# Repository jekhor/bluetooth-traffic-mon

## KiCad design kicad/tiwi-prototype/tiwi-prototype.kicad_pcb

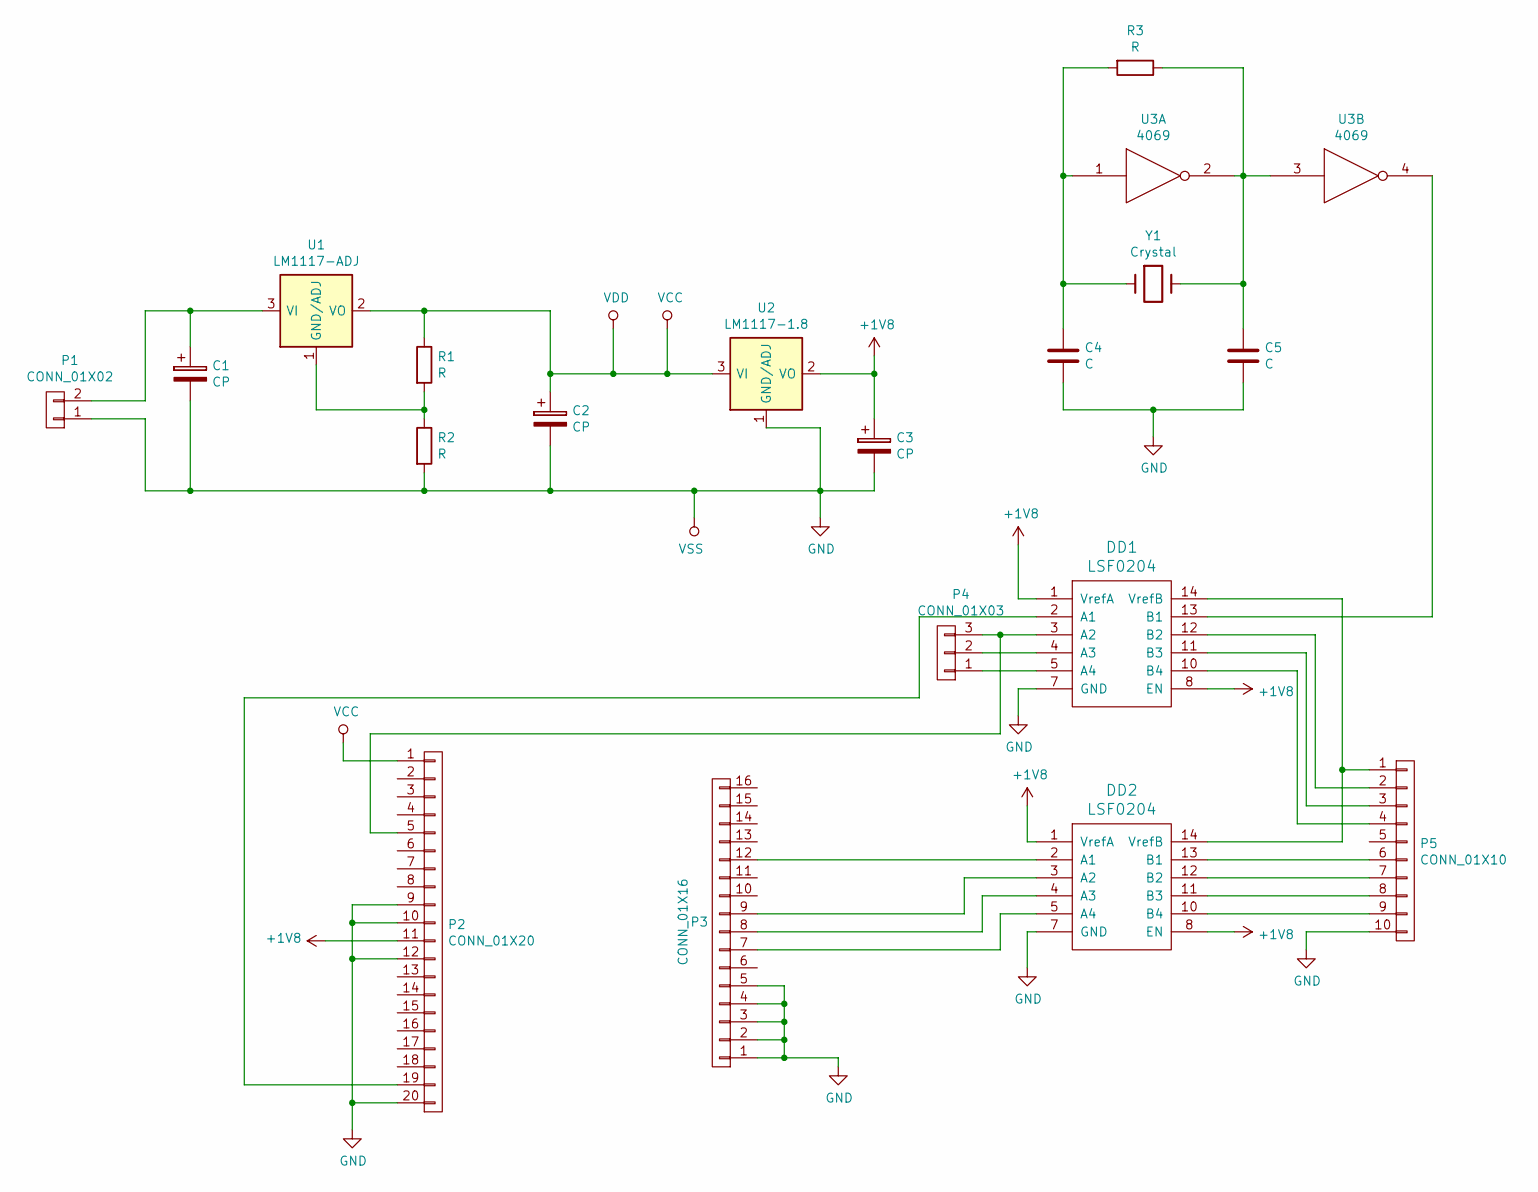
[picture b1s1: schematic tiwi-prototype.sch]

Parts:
C1, C2, C3: CP; C_Radial_D8_L13_P3.8
C4, C5: C; C_0805
DD1, DD2: LSF0204; SSOP-14
P1: CONN_01X02; Pin_Header_Straight_1x02
P2: CONN_01X20; Socket_Strip_Straight_1x20
P3: CONN_01X16; Socket_Strip_Straight_1x16
P4: CONN_01X03; Pin_Header_Straight_1x03
P5: CONN_01X10; Pin_Header_Straight_1x10
R1, R2, R3: R; R_0805
U1: LM1117-ADJ; SOT-223
U2: LM1117-1.8; SOT-223
U3: 4069; DIP-14_W7.62mm_LongPads
Y1: Crystal; Crystal_Round_Vertical_3mm_BigPad

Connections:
+1V8: C3.1, DD1.1 (VrefA), DD1.8 (EN), DD2.1 (VrefA), DD2.8 (EN), P2.11, U2.2 (VO), U2.4 (VO)
GND: C1.2, C2.2, C3.2, C4.2, C5.2, DD1.7 (GND), DD2.7 (GND), P1.1, P2.9, P2.10, P2.12, P2.20, P3.1, P3.2, P3.3, P3.4, P3.5, P5.10, R2.2, U2.1 (GND/ADJ), U3.7 (VSS)
unnamed: C1.1, P1.2, U1.3 (VI)
unnamed: C4.1, R3.2, U3.1, Y1.1
unnamed: C5.1, R3.1, U3.2, U3.3, Y1.2
unnamed: DD1.2 (A1), P2.19
unnamed: DD1.3 (A2), P2.5, P4.3
unnamed: DD1.4 (A3), P4.2
unnamed: DD1.5 (A4), P4.1
unnamed: DD1.10 (B4), P5.4
unnamed: DD1.11 (B3), P5.3
unnamed: DD1.12 (B2), P5.2
unnamed: DD1.13 (B1), U3.4
unnamed: DD1.14 (VrefB), DD2.14 (VrefB), P5.1
unnamed: DD2.2 (A1), P3.12
unnamed: DD2.3 (A2), P3.9
unnamed: DD2.4 (A3), P3.8
unnamed: DD2.5 (A4), P3.7
unnamed: DD2.10 (B4), P5.9
unnamed: DD2.11 (B3), P5.8
unnamed: DD2.12 (B2), P5.7
unnamed: DD2.13 (B1), P5.6
unnamed: R1.2, R2.1, U1.1 (GND/ADJ)
VCC: C2.1, P2.1, R1.1, U1.2 (VO), U1.4 (VO), U2.3 (VI), U3.14 (VDD)

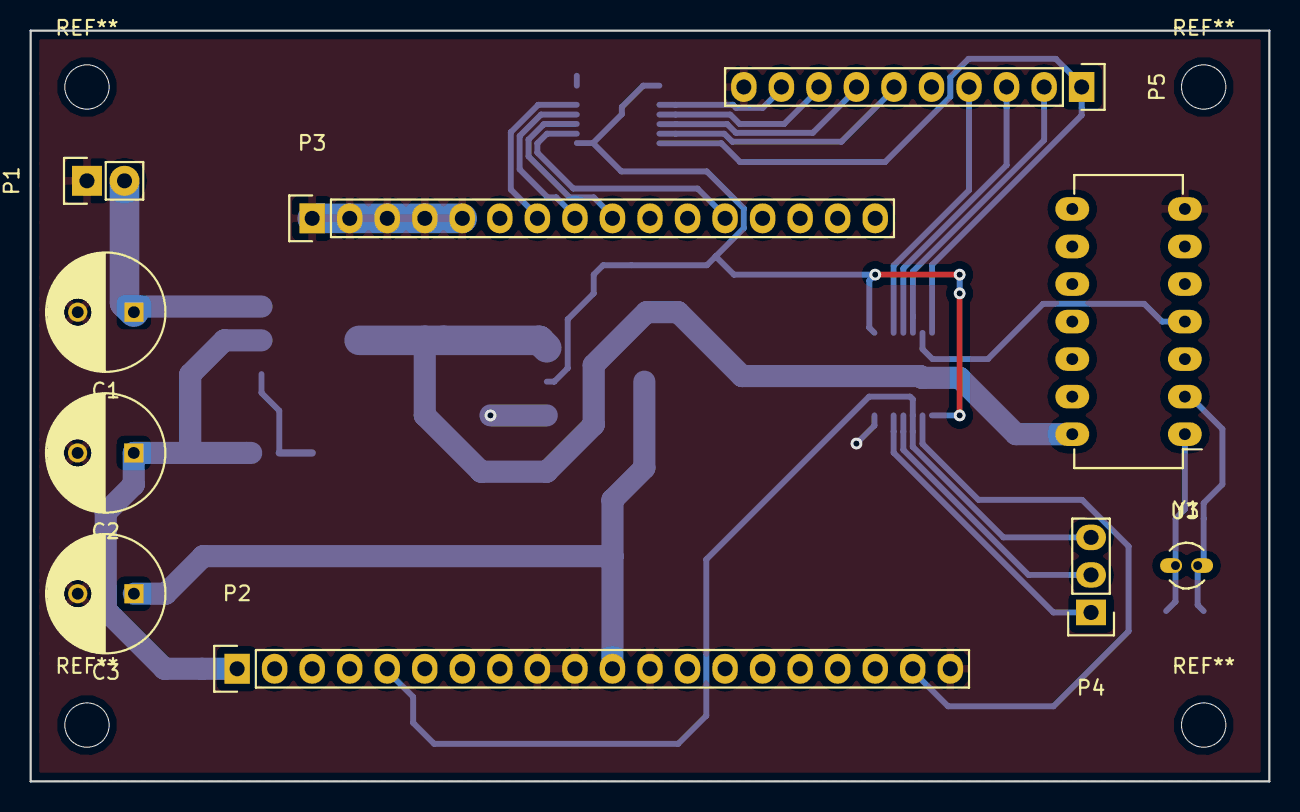
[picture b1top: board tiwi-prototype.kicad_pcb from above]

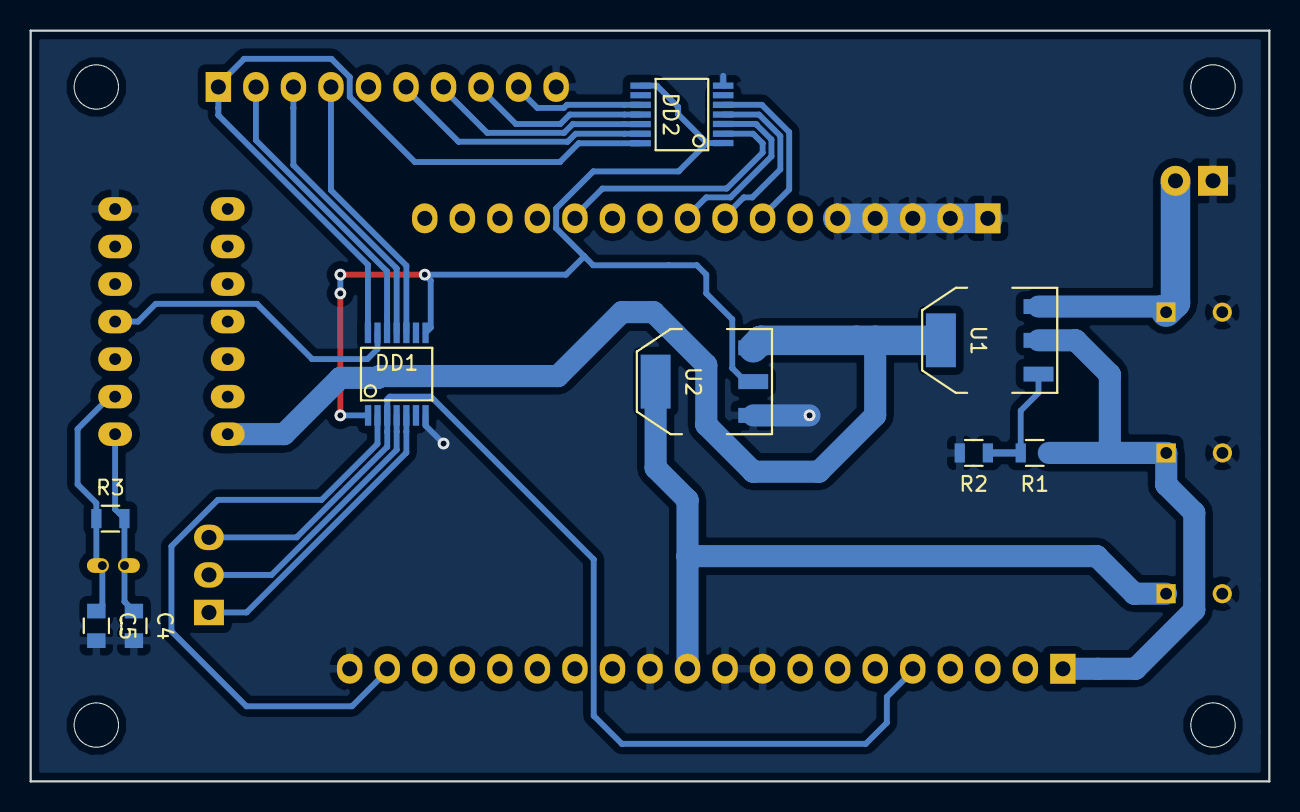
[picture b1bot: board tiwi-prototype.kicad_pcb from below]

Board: 2 copper layers, 83.8 x 50.8 mm, 19 parts (9 on the bottom side), 24 nets.

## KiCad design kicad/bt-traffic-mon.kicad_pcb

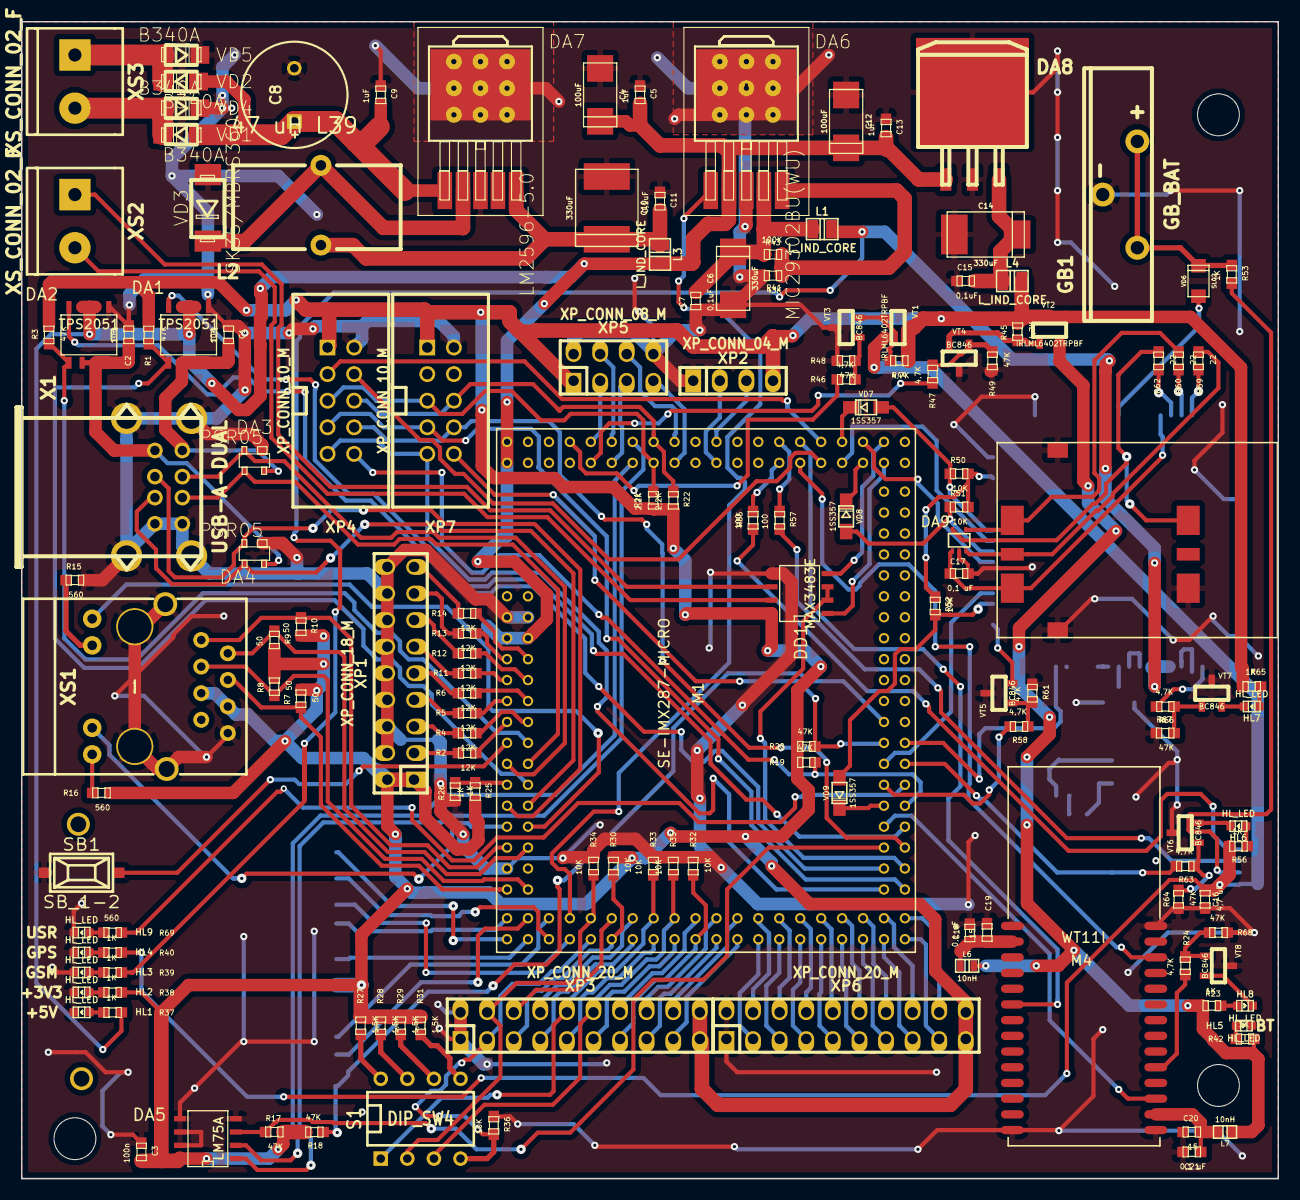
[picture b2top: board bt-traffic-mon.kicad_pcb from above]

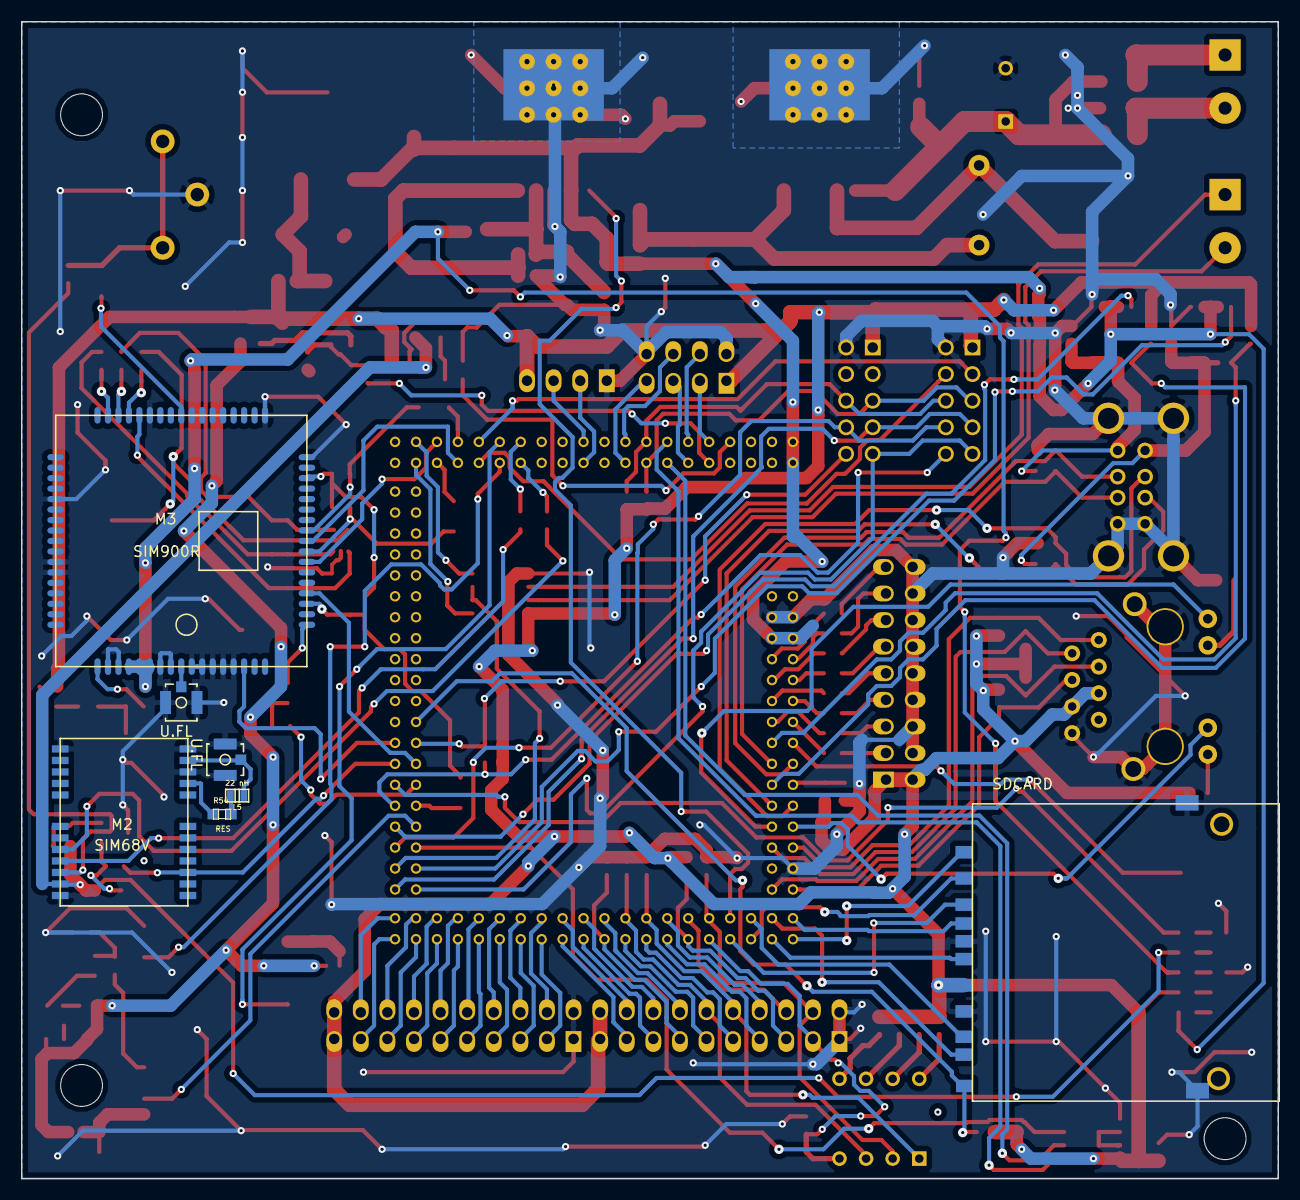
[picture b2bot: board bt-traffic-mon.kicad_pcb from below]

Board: 2 copper layers, 120.0 x 110.5 mm, 155 parts (7 on the bottom side), 181 nets.

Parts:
C1, C2: 10n; SMD_C_0603
C3: 100n; SMD_C_0603
C4, C12: 100uF; SMD_c_tant_C
C5, C9, C13: 1uF; SMD_C_0603
C6: 330uF; SMD_c_tant_C
C7, C11, C15: 0,1uF; SMD_C_0603
C8: 680uF; CP_R_100_2
C10: 330uF; SMD_c_tant_E
C14: 330uF; SMD_c_tant_D
C16: 4,7 uF; SMD_C_0603
C17, C18, C21: 0,1 uF; SMD_C_0603
C19, C20: 15; SMD_C_0603
DA1, DA2: TPS2051; SMD_SO8N_50_150
DA3, DA4: PSR05; SMD_SOT143
DA5: LM75A; SMD_SO8N_50_150
DA6: MIC29302BU(WU); SMD_TO263_5
DA7: LM2596-5.0; SMD_TO263_5
DA8: MIC29150-3.3BU(WU); SMD_TO263-3
DA9: ESDA6V1W5; SOT-353
DD1: MAX3483E; SMD_SO8N_50_150
GB1: GB_BAT; DISCRET_BAT_CR2032V
HL1, HL2, HL3, HL4, HL5, HL6, HL7, HL8, HL9: HL_LED; SMD_Led_0603
L1, L3, L4: L_IND_CORE; SMD_IND_0805
L2: 47 uH L39; DISCRET_IND_Toroid_8x16mm_V
L5: 22 nH; SMD_IND_0603
L6, L7: 10nH; SMD_IND_0603
M1: SE-IMX287-MICRO; SE-iMX287-Micro
M2: SIM68V
M3: SIM900R; SIM900
M4: WT11I; WT11i
R1, R3, R17, R18, R19, R20, R48, R49, R61, R64, R67, R68: 47K; SMD_R_0603
R2, R4, R5, R6, R11, R12, R13, R14: 12K; SMD_R_0603
R7, R8, R9, R10: 50; SMD_R_0603
R15, R16, R69: 560; SMD_R_0603
R21, R22: 2,2K; SMD_R_0603
R23, R25, R26, R37, R38, R39, R40, R42, R53, R56, R65: 1K; SMD_R_0603
R24, R44, R45, R46, R47, R58, R63, R66: 4,7K; SMD_R_0603
R27, R28, R29, R31: 1,5K; SMD_R_0603
R30, R32, R33, R34, R35, R36, R50, R51, R52: 10K; SMD_R_0603
R41: 100K; SMD_R_0603
R43: 43K; SMD_R_0603
R54: RES; SMD_R_0603
R55, R57: 100; SMD_R_0603
R59, R60, R62: 22; SMD_R_0603
S1: DIP_SW4; DIP-8__300
SB1: SB_1-2; SMD_SWT_push
VD1, VD2, VD4, VD5: B340A; SMD_DO214AC_SMA
VD3: SK35/MBRS360; SMD_DO214AB_SMC
VD6: SL02; SMD_DO219AB
VD7, VD8, VD9: 1SS357; SMD_SOD323_W
VT1, VT2: IRLML6402TRPBF; SMD_SOT23_3
VT3, VT4, VT5, VT6, VT7, VT8: BC846; SMD_SOT23_3
X1: USB-A-DUAL; CONN_usb_Ax2
X2: SDCARD; SMD_SOCKET_SDCARD_SD-03
X3: 47388-2001
XP1: XP_CONN_18_M; CONN_PLD-18
XP2: XP_CONN_04_M; CONN_PLS-4
XP3, XP6: XP_CONN_20_M; CONN_PLD-20
XP4, XP7: XP_CONN_10_M; CONN_BH-10
XP5: XP_CONN_08_M; CONN_PLD-8
XS1: HR911105A; CONN_RJ45ETH
XS2, XS3: XS_CONN_02_F; CONN_TERM_2p
XW1, XW2: U.FL; u.FL

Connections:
+3.3V: C3.2, DA5.8, DD1.8, L4.2, R1.2, R3.2, R7.2, R8.2, R9.2, R10.2, R16.2, R17.2, R18.2, R19.2, R20.2, R21.2, R22.2, R25.2, R27.2, R28.2, R29.2, R30.2, R31.2, R38.1, R44.2, R45.2, R65.2, VT1.3, VT2.3, X2.5, XP1.1, XP1.2, XP2.4, XP3.19, XP3.20, XP4.1, XP5.1, XP6.19, XP6.20, XP7.1, XS1.5, XS1.6
+5V: C4.1, C5.2, C12.1, C13.2, DA1.2, DA1.3, DA2.2, DA2.3, DA6.2, DA8.1, L3.2, M1.119, M1.120, M1.125, M1.126, R37.1
/IO/ADC0: M1.129, R12.2
/IO/ADC1: M1.132, R5.2
/IO/ADC2: M1.128, R13.2
/IO/ADC3: M1.133, R4.2
/IO/ADC4: M1.134, R2.2
/IO/ADC5: M1.127, R14.2
/IO/ADC6: M1.130, R11.2
/IO/ADC7: M1.131, R6.2
/IO/DUART_RXD: M1.99, XP2.2
/IO/DUART_TXD: M1.100, XP2.3
/IO/ETH_LED0: M1.143, XS1.9
/IO/ETH_LED1: M1.144, XS1.11
/IO/ETH_RD+: M1.149, R8.1, XS1.3
/IO/ETH_RD-: M1.150, R7.1, XS1.4
/IO/ETH_TD+: M1.146, R10.1, XS1.1
/IO/ETH_TD-: M1.145, R9.1, XS1.2
/IO/GPIO0: M1.16, R33.2, S1.1, XP3.10
/IO/GPIO1: M1.10, R34.2, S1.2, XP3.4
/IO/GPIO2: M1.18, R35.2, S1.3, XP3.12
/IO/GPIO3: M1.9, R36.2, S1.4, XP3.3
/IO/GPIO4: M1.19, R32.1, XP3.13
/IO/GPIO5: M1.12, XP3.6
/IO/GPIO6: M1.21, XP3.15
/IO/GPIO7: M1.22, XP3.16
/IO/GPIO8: M1.23, XP3.17
/IO/GPIO9: M1.29, XP6.7
/IO/GPIO10: M1.24, XP3.18
/IO/GPIO11: M1.25, XP6.3
/IO/GPIO12: M1.26, XP6.4
/IO/GPIO13: M1.27, XP6.5
/IO/GPIO14: M1.28, XP6.6
/IO/GPIO15: M1.32, XP6.10
/IO/GPIO16: M1.31, XP6.9
/IO/GPIO17: M1.30, XP6.8
/IO/GPIO18: M1.36, XP6.14
/IO/GPIO19: M1.35, XP6.13
/IO/GPIO20: M1.34, XP6.12
/IO/GPIO21: M1.40, XP6.18
/IO/GPIO22: M1.39, XP6.17
/IO/GPIO23: M1.38, XP6.16
/IO/GPIO24: M1.33, XP6.11
/IO/GPIO25: M1.14, XP3.8
/IO/GPIO26: M1.11, R30.1, XP3.5
/IO/GPIO27: M1.37, XP6.15
/IO/GPIO28: M1.15, XP3.9
/IO/GPIO29: M1.17, XP3.11
/IO/GPIO30: M1.20, XP3.14
/IO/GPIO31: M1.13, XP3.7
/IO/I2C0_SCL: DA5.2, M1.107
/IO/I2C0_SDA: DA5.1, M1.108
/IO/LM75_OS: DA5.3, M1.46, R17.1
/IO/PWM3: M1.103, XP5.7
/IO/PWM4: M1.104, XP5.6
/IO/PWM5: M1.110, XP5.4
/IO/PWM6: M1.112, XP5.3
/IO/PWM7: M1.109, XP5.5
/IO/RS485_RX: DD1.1, M1.83
/IO/RS485_TX: DD1.4, M1.84
/IO/RS485_~RE~/DE: DD1.2, DD1.3, M1.43
/IO/SD_CD: M1.2, X2.11
/IO/SD_CLK: M1.3, X2.4
/IO/SD_CMD: M1.7, X2.2
/IO/SD_DAT0: M1.6, X2.7
/IO/SD_DAT1: M1.4, X2.8
/IO/SD_DAT2: M1.1, X2.9
/IO/SD_DAT3: M1.5, X2.1
/IO/SD_WP: M1.58, R18.1, X2.10
/IO/UEXT1_RX: M1.89, XP4.4
/IO/UEXT1_SSEL: M1.49, R19.1, XP4.10
/IO/UEXT1_TX: M1.90, XP4.3
/IO/UEXT2_SSEL: M1.56, R20.1, XP7.10
/IO/UEXT_MISO: M1.41, XP4.7, XP7.7
/IO/UEXT_MOSI: M1.45, XP4.8, XP7.8
/IO/UEXT_SCK: M1.42, XP4.9, XP7.9
/IO/UEXT_SCL: M1.105, R21.1, XP4.5, XP7.5
/IO/UEXT_SDA: M1.106, R22.1, XP4.6, XP7.6
/IO/USB0_D+: DA3.3, M1.137, X1.7
/IO/USB0_D-: DA3.2, M1.138, X1.6
/IO/USB0_PWR_EN: DA1.4, M1.47
/IO/USB1_D+: DA4.3, M1.141, X1.3
/IO/USB1_D-: DA4.2, M1.142, X1.2
/IO/USB1_PWR_EN: DA2.4, M1.44
/IO/~USB0_OVC~: DA1.5, M1.139, R1.1
/IO/~USB1_OVC~: DA2.5, M1.135, R3.1
/Main CPU module/BT_PWR_EN: M1.111, R47.2
/Main CPU module/BT_RESET: M1.48, M4.17
/Main CPU module/BT_RXD: M1.92, M4.6
/Main CPU module/BT_TXD: M1.91, M4.26
/Main CPU module/GPS_PPS: M1.53, M2.3, R63.2
/Main CPU module/GPS_PWR_EN: M1.114, R46.2
/Main CPU module/GPS_RXD: M1.94, R57.1
/Main CPU module/GPS_TXD: M1.93, R55.1
/Main CPU module/GSM_CTS: M1.86, M3.7
/Main CPU module/GSM_DTR: M1.50, VD9.1
/Main CPU module/GSM_PWRKEY: M1.52, R58.2
/Main CPU module/GSM_PWR_EN: DA6.1, M1.8
/Main CPU module/GSM_RI: M1.54, M3.4
/Main CPU module/GSM_RTS: M1.85, VD8.1
/Main CPU module/GSM_RXD: M1.88, VD7.1
/Main CPU module/GSM_STATUS: M1.55, M3.66
/Main CPU module/GSM_TXD: M1.87, M3.9
/Power/BT_PWR: L6.2, L7.1, R23.2, R42.1, VT2.2
/Power/GPS_PWR: C16.2, M2.23, R40.1, R56.2, VT1.2
/Power/GSM_PWR: L1.2, M3.55, M3.56, M3.57, R39.1
unnamed: C1.2, DA1.6, DA1.7, DA1.8, DA3.4, X1.5
unnamed: C2.2, DA2.6, DA2.7, DA2.8, DA4.4, X1.1
unnamed: C6.1, C7.2, DA6.4, L1.1, R41.2
unnamed: C8.1, C9.2, DA7.1, VD1.2, VD2.2
unnamed: C10.1, C11.2, DA7.5, L2.2, L3.1
unnamed: C14.1, C15.2, DA8.3, L4.1
unnamed: C17.1, DA9.1, M3.30, X3.1
unnamed: C18.2, C19.2, L6.1, M4.2
unnamed: C20.2, C21.2, L7.2, M4.16
unnamed: DA6.5, R41.1, R43.2
unnamed: DA7.2, L2.1, VD3.1
unnamed: DA9.3, R59.2, X3.2
unnamed: DA9.4, R60.2, X3.3
unnamed: DA9.5, R62.2, X3.7
unnamed: DD1.6, XS2.1
unnamed: DD1.7, XS2.2
unnamed: GB1.1, R53.1, VD6.1
unnamed: HL1.2, R37.2
unnamed: HL2.2, R38.2
unnamed: HL3.2, R39.2
unnamed: HL4.2, R40.2
unnamed: HL5.2, R42.2
unnamed: HL6.1, VT6.2
unnamed: HL6.2, R56.1
unnamed: HL7.1, VT7.2
unnamed: HL7.2, R65.1
unnamed: HL8.1, VT8.2
unnamed: HL8.2, R23.1
unnamed: HL9.2, R69.2
unnamed: L5.1, M2.11, XW2.1
unnamed: L5.2, R54.2
unnamed: M1.51, R69.1
unnamed: M1.136, SB1.2
unnamed: M1.140, R25.1, R26.2
unnamed: M2.9, R54.1
unnamed: M2.20, R55.2
unnamed: M2.21, R57.2
unnamed: M2.22, R53.2
unnamed: M3.1, VT5.2
unnamed: M3.3, R52.1, VD9.2
unnamed: M3.8, R51.1, VD8.2
unnamed: M3.10, R50.1, VD7.2
unnamed: M3.15, R50.2, R51.2, R52.2
unnamed: M3.26, VD6.2
unnamed: M3.31, R62.1
unnamed: M3.32, R60.1
unnamed: M3.33, R59.1
unnamed: M3.52, R66.2
unnamed: M3.60, XW1.1
unnamed: M4.19, R24.2
unnamed: R2.1, XP1.3
unnamed: R4.1, XP1.5
unnamed: R5.1, XP1.7
unnamed: R6.1, XP1.9
unnamed: R11.1, XP1.11
unnamed: R12.1, XP1.13
unnamed: R13.1, XP1.15
unnamed: R14.1, XP1.17
unnamed: R15.1, XS1.10
unnamed: R16.1, XS1.12
unnamed: R24.1, R68.2, VT8.1
unnamed: R27.1, S1.8
unnamed: R28.1, S1.7
unnamed: R29.1, S1.6
unnamed: R31.1, S1.5
unnamed: R44.1, VT1.1, VT3.2
unnamed: R45.1, VT2.1, VT4.2
unnamed: R46.1, R48.2, VT3.1
unnamed: R47.1, R49.2, VT4.1
unnamed: R58.1, R61.2, VT5.1
unnamed: R63.1, R64.2, VT6.1
unnamed: R66.1, R67.2, VT7.1
unnamed: VD1.1, VD4.2, XS3.2
unnamed: VD2.1, VD5.2, XS3.1
~: C1.1, C2.1, C3.1, C4.2, C5.1, C6.2, C7.1, C8.2, C9.1, C10.2, C11.1, C12.2, C13.1, C14.2, C15.1, C16.1, C17.2, C18.1, C19.1, C20.1, C21.1, DA1.1, DA2.1, DA3.1, DA4.1, DA5.4, DA5.5, DA5.6, DA5.7, DA6.3, DA7.3, DA8.2, DA9.2, DD1.5, GB1.2, HL1.1, HL2.1, HL3.1, HL4.1, HL5.1, HL9.1, M1.123, M1.124, M1.148, M2.10, M2.12, M2.13, M2.24, M3.17, M3.18, M3.29, M3.39, M3.45, M3.46, M3.53, M3.54, M3.58, M3.59, M3.61, M3.62, M3.63, M3.64, M3.65, M4.1, M4.14, M4.15, M4.28, R15.2, R26.1, R32.2, R33.1, R34.1, R35.1, R36.1, R43.1, R48.1, R49.1, R61.1, R64.1, R67.1, R68.1, SB1.1, VD3.2, VD4.1, VD5.1, VT3.3, VT4.3, VT5.3, VT6.3, VT7.3, VT8.3, X1.4, X1.8, X1.9, X1.10, X1.11, X1.12, X2.3, X2.6, X2.12, X3.5, X3.9, X3.10, XP1.4, XP1.6, XP1.8, XP1.10, XP1.12, XP1.14, XP1.16, XP1.18, XP2.1, XP3.1, XP3.2, XP4.2, XP5.2, XP5.8, XP6.1, XP6.2, XP7.2, XS1.0, XS1.8, XW1.2, XW2.2

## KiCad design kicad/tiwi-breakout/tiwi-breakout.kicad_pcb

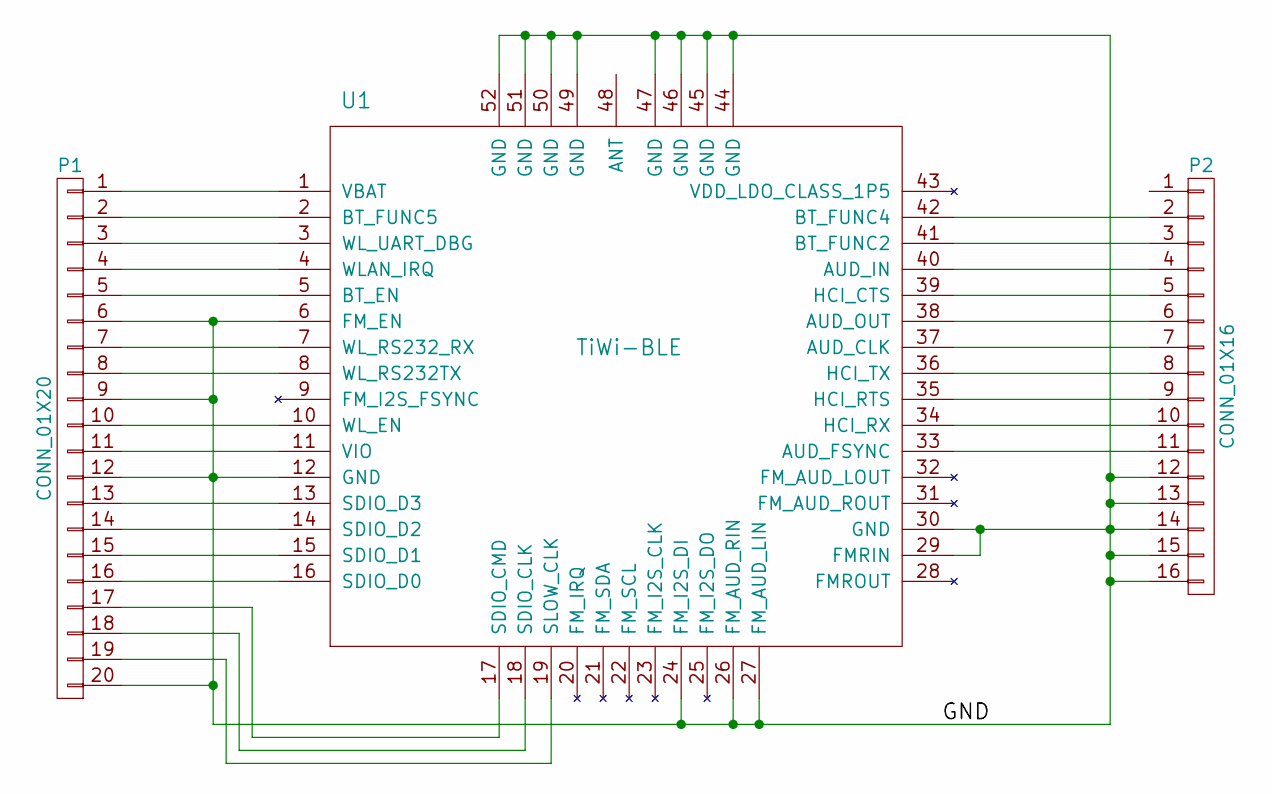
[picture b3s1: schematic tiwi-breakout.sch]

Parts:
P1: CONN_01X20; Pin_Header_Straight_1x20
P2: CONN_01X16; Pin_Header_Straight_1x16
U1: TiWi-BLE

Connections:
/GND: P1.6, P1.9, P1.12, P1.20, P2.12, P2.13, P2.14, P2.15, P2.16, U1.6 (FM_EN), U1.12 (GND), U1.24 (FM_I2S_DI), U1.26 (FM_AUD_RIN), U1.27 (FM_AUD_LIN), U1.29 (FMRIN), U1.30 (GND), U1.44 (GND), U1.45 (GND), U1.46 (GND), U1.47 (GND), U1.49 (GND), U1.50 (GND), U1.51 (GND), U1.52 (GND)
unnamed: P1.1, U1.1 (VBAT)
unnamed: P1.2, U1.2 (BT_FUNC5)
unnamed: P1.3, U1.3 (WL_UART_DBG)
unnamed: P1.4, U1.4 (WLAN_IRQ)
unnamed: P1.5, U1.5 (BT_EN)
unnamed: P1.7, U1.7 (WL_RS232_RX)
unnamed: P1.8, U1.8 (WL_RS232TX)
unnamed: P1.10, U1.10 (WL_EN)
unnamed: P1.11, U1.11 (VIO)
unnamed: P1.13, U1.13 (SDIO_D3)
unnamed: P1.14, U1.14 (SDIO_D2)
unnamed: P1.15, U1.15 (SDIO_D1)
unnamed: P1.16, U1.16 (SDIO_D0)
unnamed: P1.17, U1.17 (SDIO_CMD)
unnamed: P1.18, U1.18 (SDIO_CLK)
unnamed: P1.19, U1.19 (SLOW_CLK)
unnamed: P2.2, U1.42 (BT_FUNC4)
unnamed: P2.3, U1.41 (BT_FUNC2)
unnamed: P2.4, U1.40 (AUD_IN)
unnamed: P2.5, U1.39 (HCI_CTS)
unnamed: P2.6, U1.38 (AUD_OUT)
unnamed: P2.7, U1.37 (AUD_CLK)
unnamed: P2.8, U1.36 (HCI_TX)
unnamed: P2.9, U1.35 (HCI_RTS)
unnamed: P2.10, U1.34 (HCI_RX)
unnamed: P2.11, U1.33 (AUD_FSYNC)

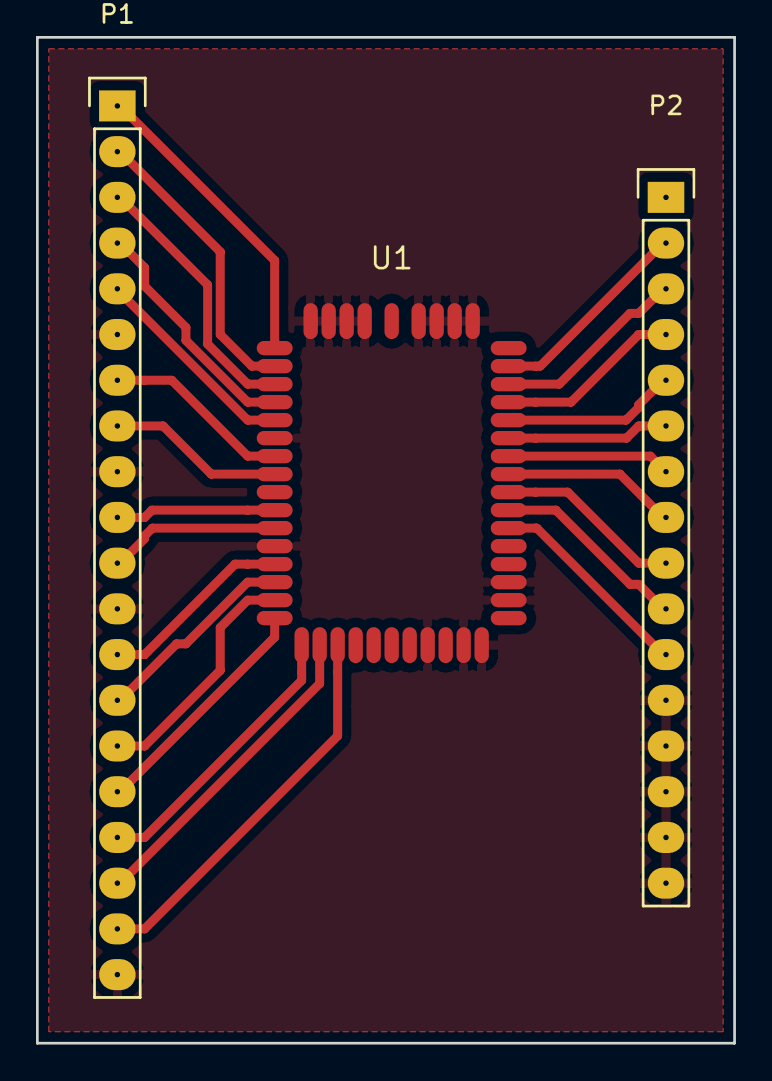
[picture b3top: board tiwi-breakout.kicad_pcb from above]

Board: 2 copper layers, 38.7 x 55.9 mm, 3 parts (0 on the bottom side), 27 nets.
